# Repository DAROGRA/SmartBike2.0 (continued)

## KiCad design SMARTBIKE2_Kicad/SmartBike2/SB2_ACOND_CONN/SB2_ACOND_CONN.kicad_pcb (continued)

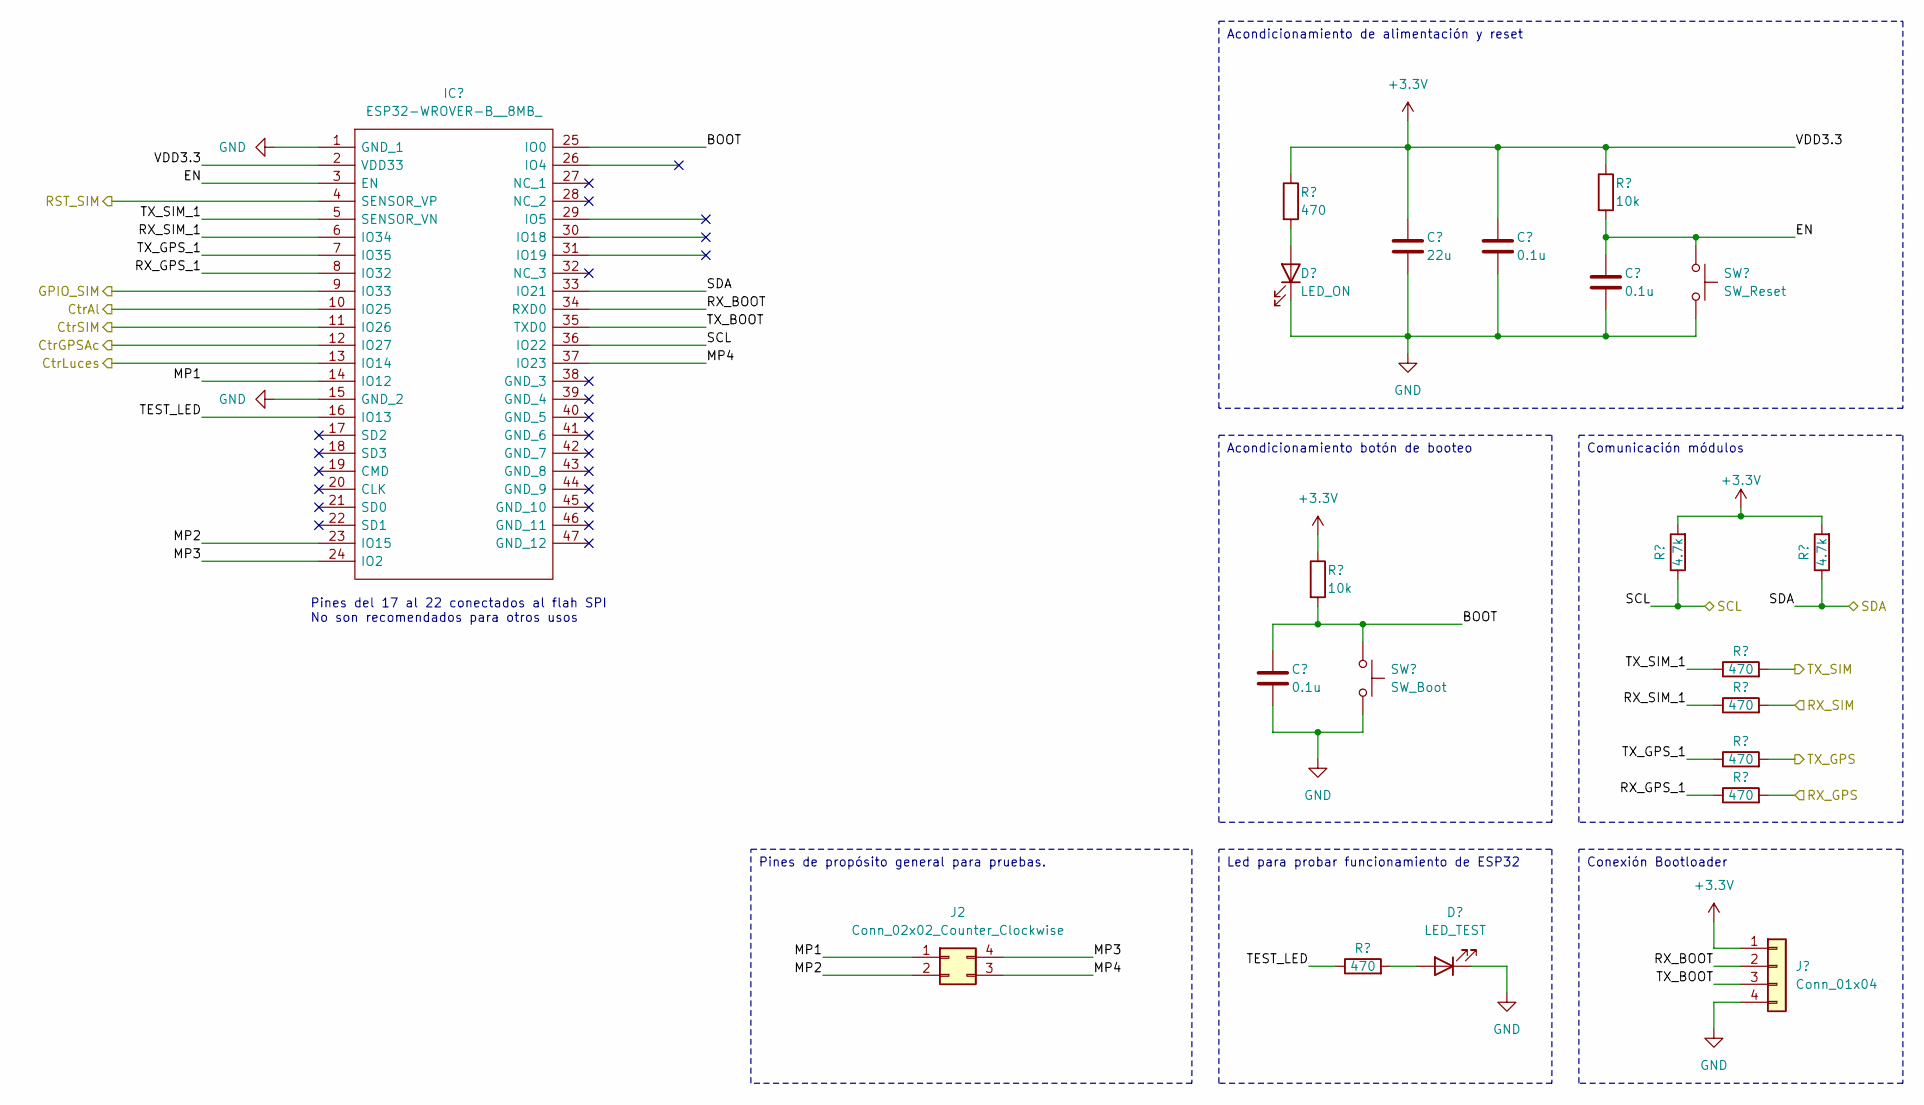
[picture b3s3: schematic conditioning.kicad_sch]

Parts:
C1, C3, C4: 0.1u; C_0805_2012Metric_Pad1.18x1.45mm_HandSolder
C2: 22u; C_0805_2012Metric_Pad1.18x1.45mm_HandSolder
D1: LED_ON; LED_1206_3216Metric_Pad1.42x1.75mm_HandSolder
D2: LED_TEST; LED_1206_3216Metric_Pad1.42x1.75mm_HandSolder
IC1: ESP32-WROVER-B__8MB_; ESP32WROVERB8MB; Manufacturer_Part_Number ESP32-WROVER-B (8MB); Mouser Part Number 356-ESP32-WRO-B(8MB)
J2: Conn_02x02_Counter_Clockwise; PinHeader_2x02_P2.54mm_Vertical
J3: Conn_01x04; PinSocket_1x04_P2.54mm_Vertical
R1, R3, R6, R7, R8, R9: 470; R_0805_2012Metric_Pad1.20x1.40mm_HandSolder
R2, R4: 10k; R_0805_2012Metric_Pad1.20x1.40mm_HandSolder
R5, R10: 4.7k; R_0805_2012Metric_Pad1.20x1.40mm_HandSolder
SW1: SW_Boot; SW_SPST_CK_RS282G05A3
SW2: SW_Reset; SW_SPST_CK_RS282G05A3

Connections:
+3.3V: C2.1, C3.1, IC1.2 (VDD33), J3.1, R1.1, R2.1, R4.1, R5.2, R10.2; also elsewhere on the board
/Acondicionamiento/BOOT: C1.1, IC1.25 (IO0), R2.2, SW1.2
/Acondicionamiento/CtrAl: IC1.10 (IO25); also elsewhere on the board
/Acondicionamiento/CtrGPSAc: IC1.12 (IO27); also elsewhere on the board
/Acondicionamiento/CtrLuces: IC1.13 (IO14); also elsewhere on the board
/Acondicionamiento/CtrSIM: IC1.11 (IO26); also elsewhere on the board
/Acondicionamiento/EN: C4.1, IC1.3 (EN), R4.2, SW2.1
/Acondicionamiento/GPIO_SIM: IC1.9 (IO33); also elsewhere on the board
/Acondicionamiento/MP1: IC1.14 (IO12), J2.1
/Acondicionamiento/MP2: IC1.23 (IO15), J2.2
/Acondicionamiento/MP3: IC1.24 (IO2), J2.4
/Acondicionamiento/MP4: IC1.37 (IO23), J2.3
/Acondicionamiento/RST_SIM: IC1.4 (SENSOR_VP); also elsewhere on the board
/Acondicionamiento/RX_BOOT: IC1.34 (RXD0), J3.2
/Acondicionamiento/RX_GPS: R9.2; also elsewhere on the board
/Acondicionamiento/RX_GPS_1: IC1.8 (IO32), R9.1
/Acondicionamiento/RX_SIM: R7.2; also elsewhere on the board
/Acondicionamiento/RX_SIM_1: IC1.6 (IO34), R7.1
/Acondicionamiento/SCL: IC1.36 (IO22), R5.1; also elsewhere on the board
/Acondicionamiento/SDA: IC1.33 (IO21), R10.1; also elsewhere on the board
/Acondicionamiento/TEST_LED: IC1.16 (IO13), R3.1
/Acondicionamiento/TX_BOOT: IC1.35 (TXD0), J3.3
/Acondicionamiento/TX_GPS: R8.2; also elsewhere on the board
/Acondicionamiento/TX_GPS_1: IC1.7 (IO35), R8.1
/Acondicionamiento/TX_SIM: R6.2; also elsewhere on the board
/Acondicionamiento/TX_SIM_1: IC1.5 (SENSOR_VN), R6.1
GND: C1.2, C2.2, C3.2, C4.2, D1.1 (K), D2.1 (K), IC1.1 (GND_1), IC1.15 (GND_2), J3.4, SW1.1, SW2.2; also elsewhere on the board
unnamed: D1.2 (A), R1.2
unnamed: D2.2 (A), R3.2

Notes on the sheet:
Acondicionamiento de alimentación y reset
Led para probar funcionamiento de ESP32
Comunicación módulos
Conexión Bootloader
Acondicionamiento botón de booteo
Pines de propósito general para pruebas.
Pines del 17 al 22 conectados al flah SPI No son recomendados para otros usos

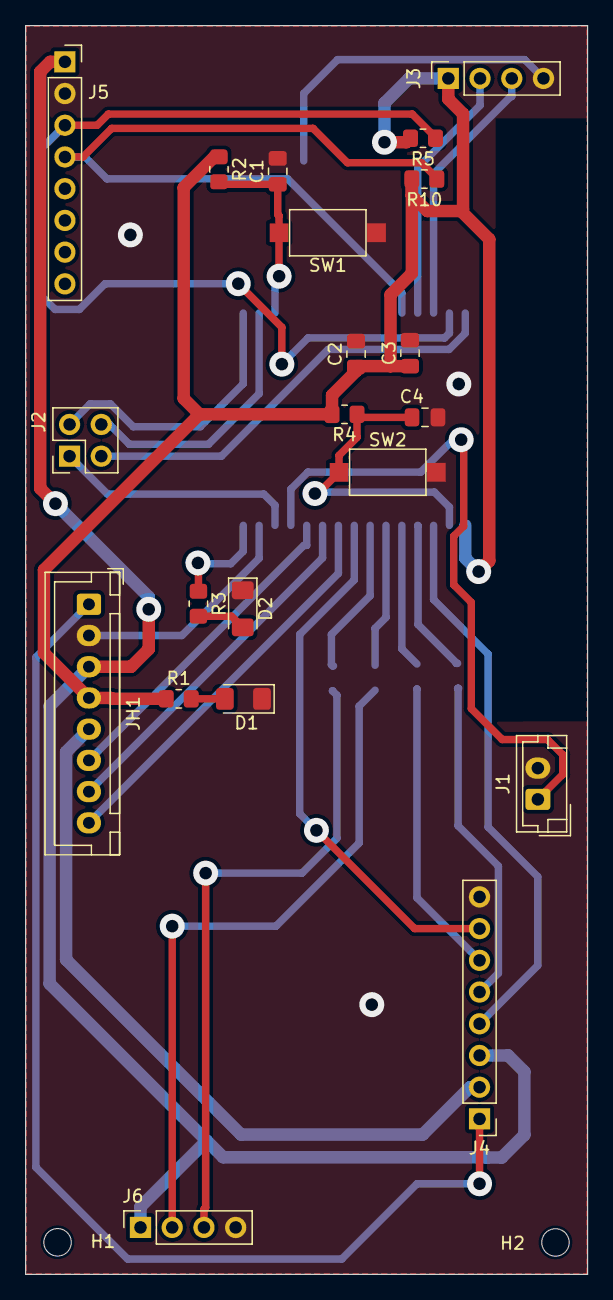
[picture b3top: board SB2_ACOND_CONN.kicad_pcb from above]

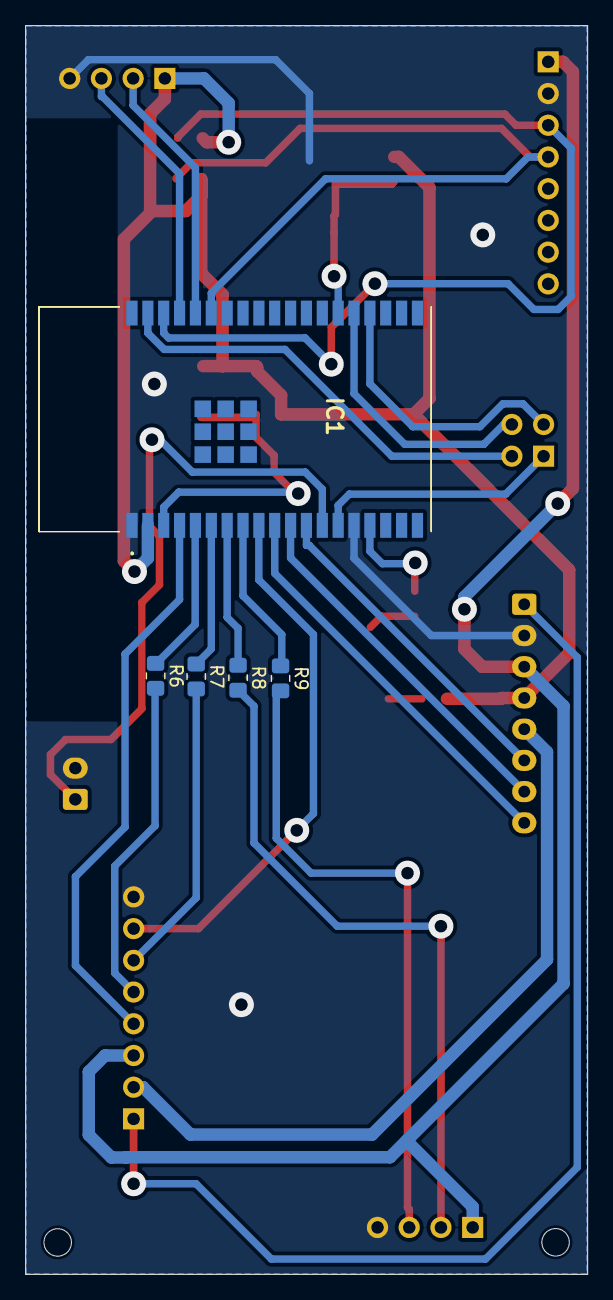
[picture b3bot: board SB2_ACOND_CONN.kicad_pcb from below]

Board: 2 copper layers, 45.0 x 100.0 mm, 28 parts (5 on the bottom side), 32 nets.

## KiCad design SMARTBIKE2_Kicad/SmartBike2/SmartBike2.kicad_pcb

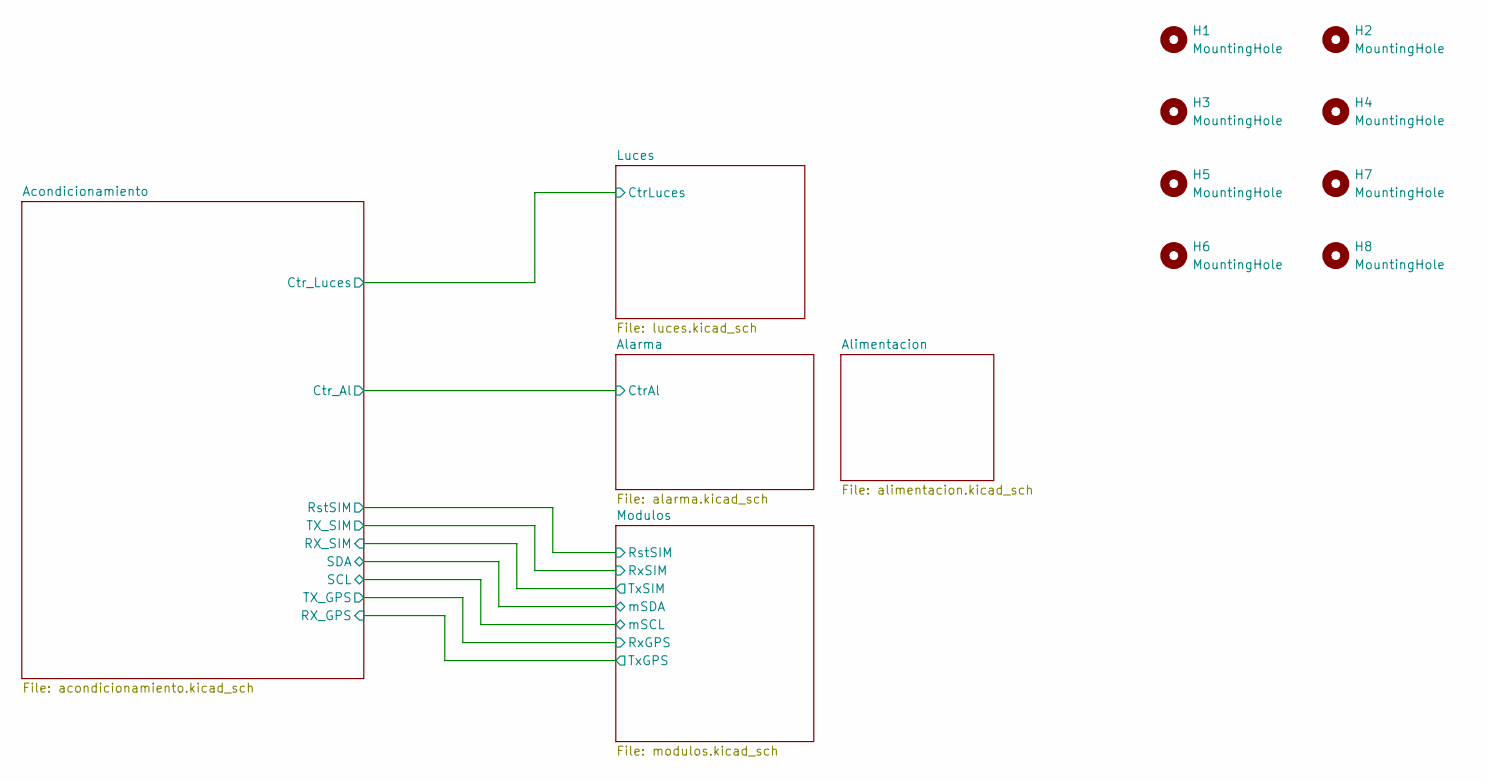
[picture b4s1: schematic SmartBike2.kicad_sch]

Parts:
H1, H2, H3, H4, H5, H6, H7, H8: MountingHole; MountingHole_3.2mm_M3

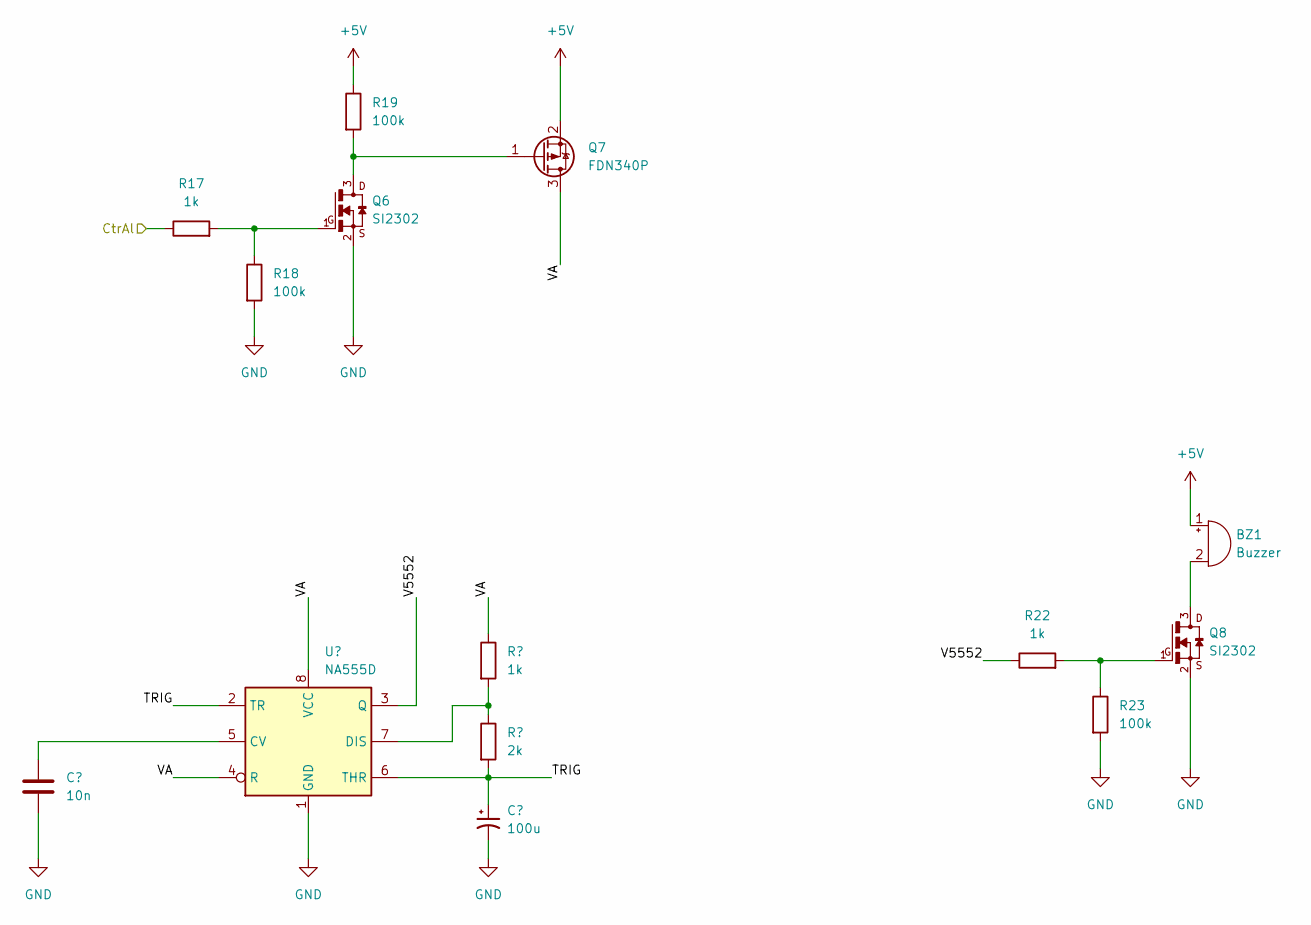
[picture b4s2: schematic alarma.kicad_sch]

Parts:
BZ1: Buzzer; PinHeader_1x02_P2.54mm_Vertical
C12: 10n; C_0805_2012Metric_Pad1.18x1.45mm_HandSolder
C13: 100u; CP_Elec_6.3x5.4
Q6, Q8: SI2302; SOT-23
Q7: FDN340P; SuperSOT-3
R17, R20, R22: 1k; R_0805_2012Metric_Pad1.20x1.40mm_HandSolder
R18, R19, R23: 100k; R_0805_2012Metric_Pad1.20x1.40mm_HandSolder
R21: 2k; R_0805_2012Metric_Pad1.20x1.40mm_HandSolder
U5: NA555D; SOIC-8_3.9x4.9mm_P1.27mm

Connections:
+5V: BZ1.1 (-), Q7.2 (S), R19.1; also elsewhere on the board
/Acondicionamiento/Ctr_Al: R17.1; also elsewhere on the board
/Alarma/TRIG: C13.1, R21.2, U5.2 (TR), U5.6 (THR)
/Alarma/V5552: R22.1, U5.3 (Q)
/Alarma/VA: Q7.3 (D), R20.1, U5.4 (R), U5.8 (VCC)
GND: C12.2, C13.2, Q6.2, Q8.2, R18.2, R23.2, U5.1 (GND); also elsewhere on the board
unnamed: BZ1.2 (+), Q8.3
unnamed: Q6.1, R17.2, R18.1
unnamed: Q6.3, Q7.1 (G), R19.2
unnamed: Q8.1, R22.2, R23.1
unnamed: C12.1, U5.5 (CV)
unnamed: R20.2, R21.1, U5.7 (DIS)

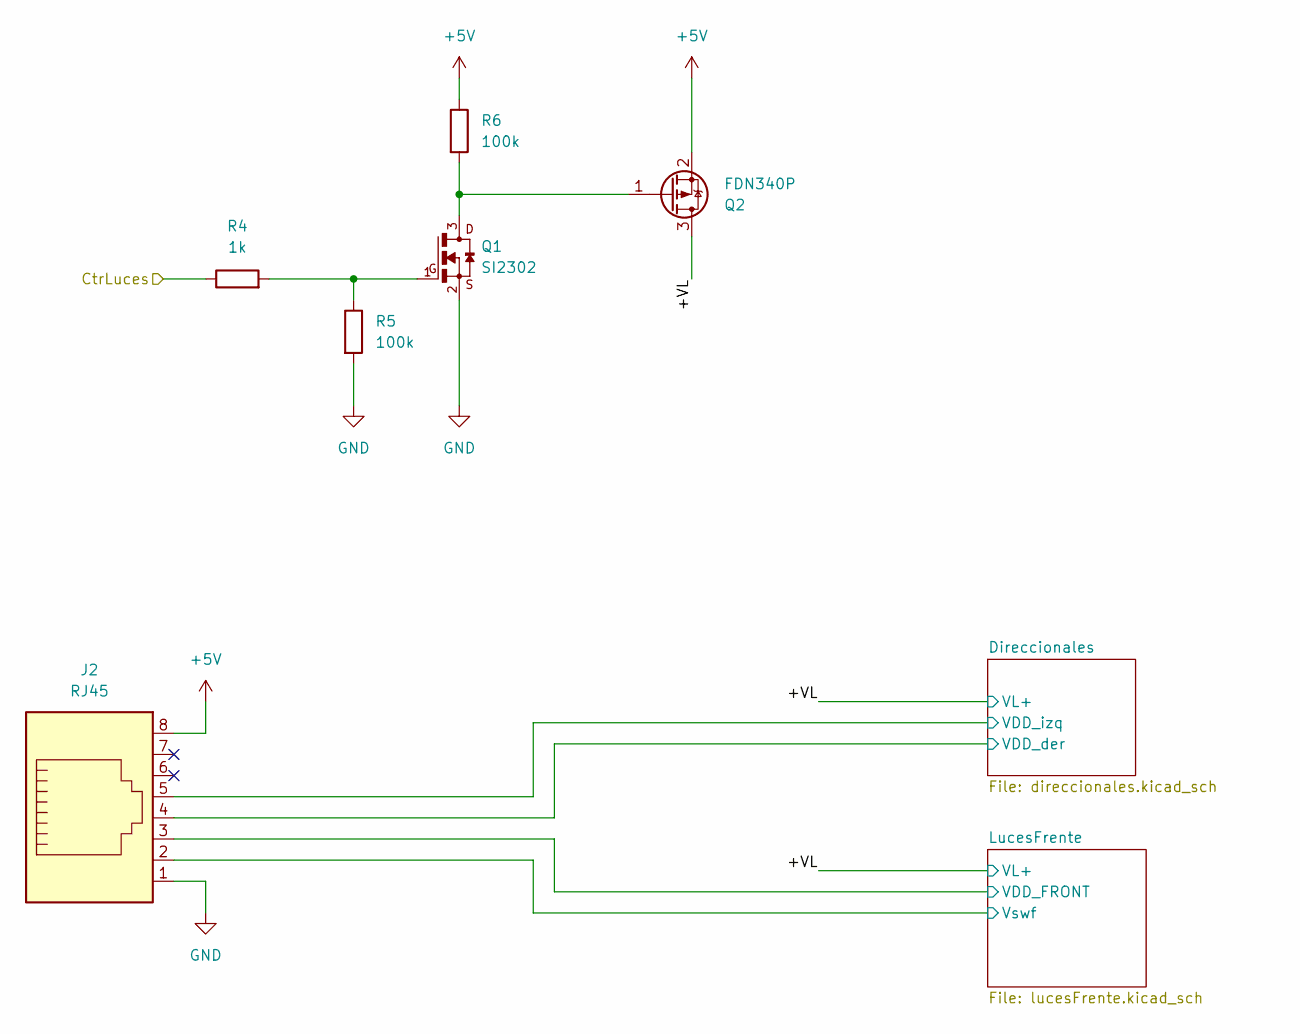
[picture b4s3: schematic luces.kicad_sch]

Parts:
J2: RJ45; RJ45_Amphenol_RJHSE538X
Q1: SI2302; SOT-23
Q2: FDN340P; SuperSOT-3
R4: 1k; R_0805_2012Metric_Pad1.20x1.40mm_HandSolder
R5, R6: 100k; R_0805_2012Metric_Pad1.20x1.40mm_HandSolder

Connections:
+5V: J2.8, Q2.2 (S), R6.1; also elsewhere on the board
/Acondicionamiento/Ctr_Luces: R4.1; also elsewhere on the board
/Luces/+VL: Q2.3 (D); also elsewhere on the board
/Luces/Direccionales/VDD_der: J2.4; also elsewhere on the board
/Luces/Direccionales/VDD_izq: J2.5; also elsewhere on the board
/Luces/LucesFrente/VDD_FRONT: J2.3; also elsewhere on the board
/Luces/LucesFrente/Vswf: J2.2; also elsewhere on the board
GND: J2.1, Q1.2, R5.2; also elsewhere on the board
unnamed: Q1.1, R4.2, R5.1
unnamed: Q1.3, Q2.1 (G), R6.2

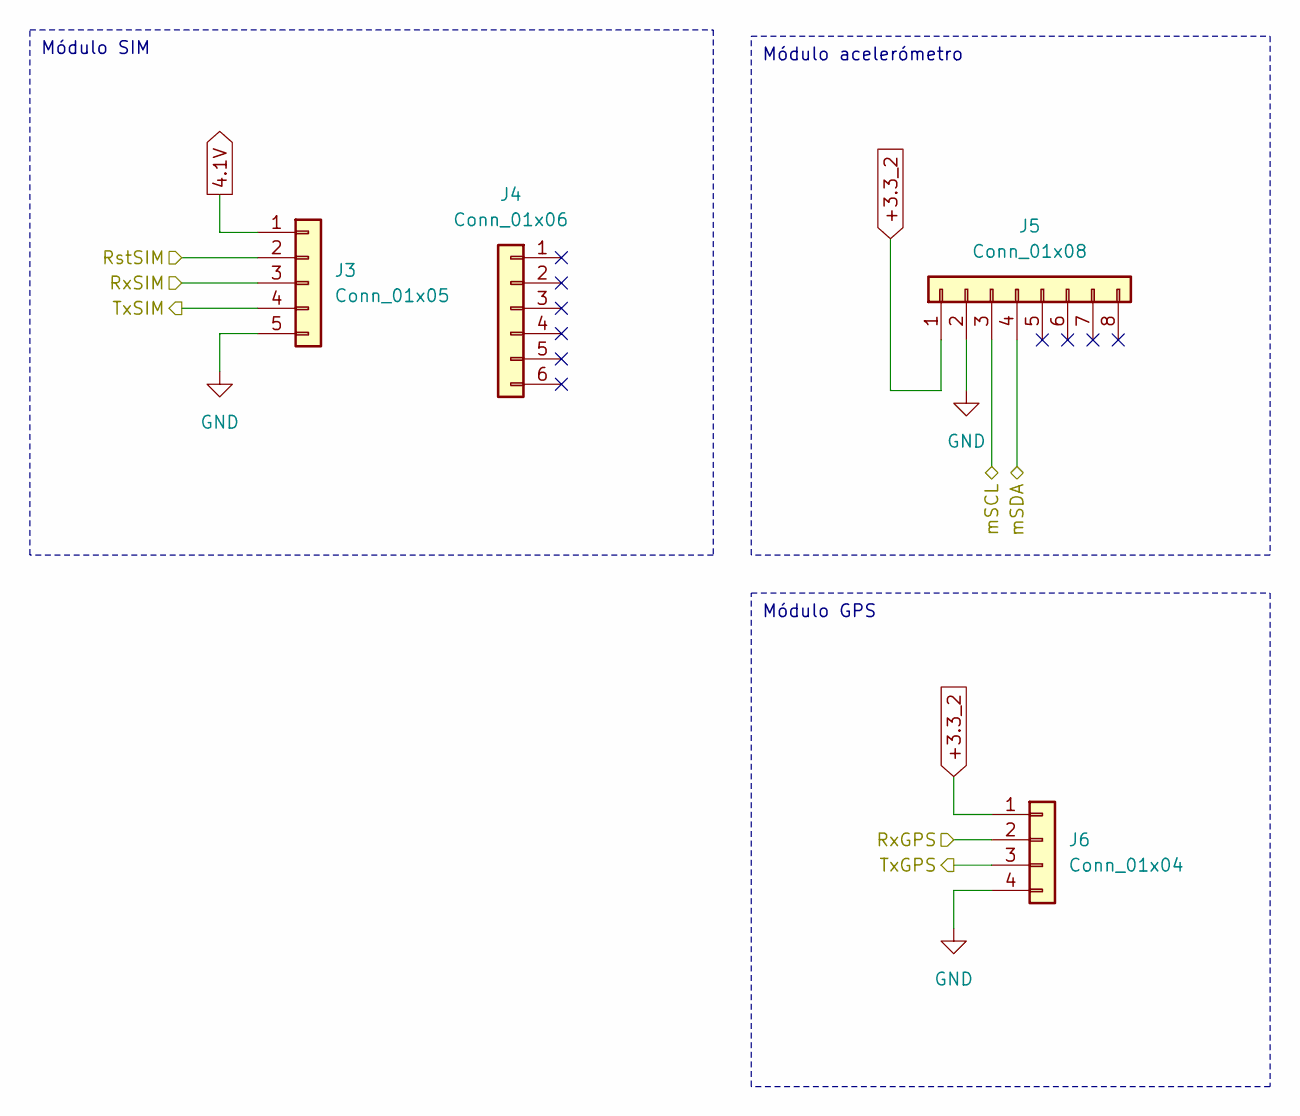
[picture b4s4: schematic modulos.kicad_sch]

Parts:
J3: Conn_01x05; PinSocket_1x05_P2.54mm_Vertical
J4: Conn_01x06; PinSocket_1x06_P2.54mm_Vertical
J5: Conn_01x08; PinSocket_1x08_P2.54mm_Vertical
J6: Conn_01x04; PinSocket_1x04_P2.54mm_Vertical

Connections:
4.1V: J3.1; also elsewhere on the board
+3.3_2: J5.1, J6.1; also elsewhere on the board
/Acondicionamiento/RX_GPS: J6.3; also elsewhere on the board
/Acondicionamiento/RX_SIM: J3.4; also elsewhere on the board
/Acondicionamiento/RstSIM: J3.2; also elsewhere on the board
/Acondicionamiento/SCL: J5.3; also elsewhere on the board
/Acondicionamiento/SDA: J5.4; also elsewhere on the board
/Acondicionamiento/TX_GPS: J6.2; also elsewhere on the board
/Acondicionamiento/TX_SIM: J3.3; also elsewhere on the board
GND: J3.5, J5.2, J6.4; also elsewhere on the board

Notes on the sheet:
Módulo GPS
Módulo SIM
Módulo acelerómetro

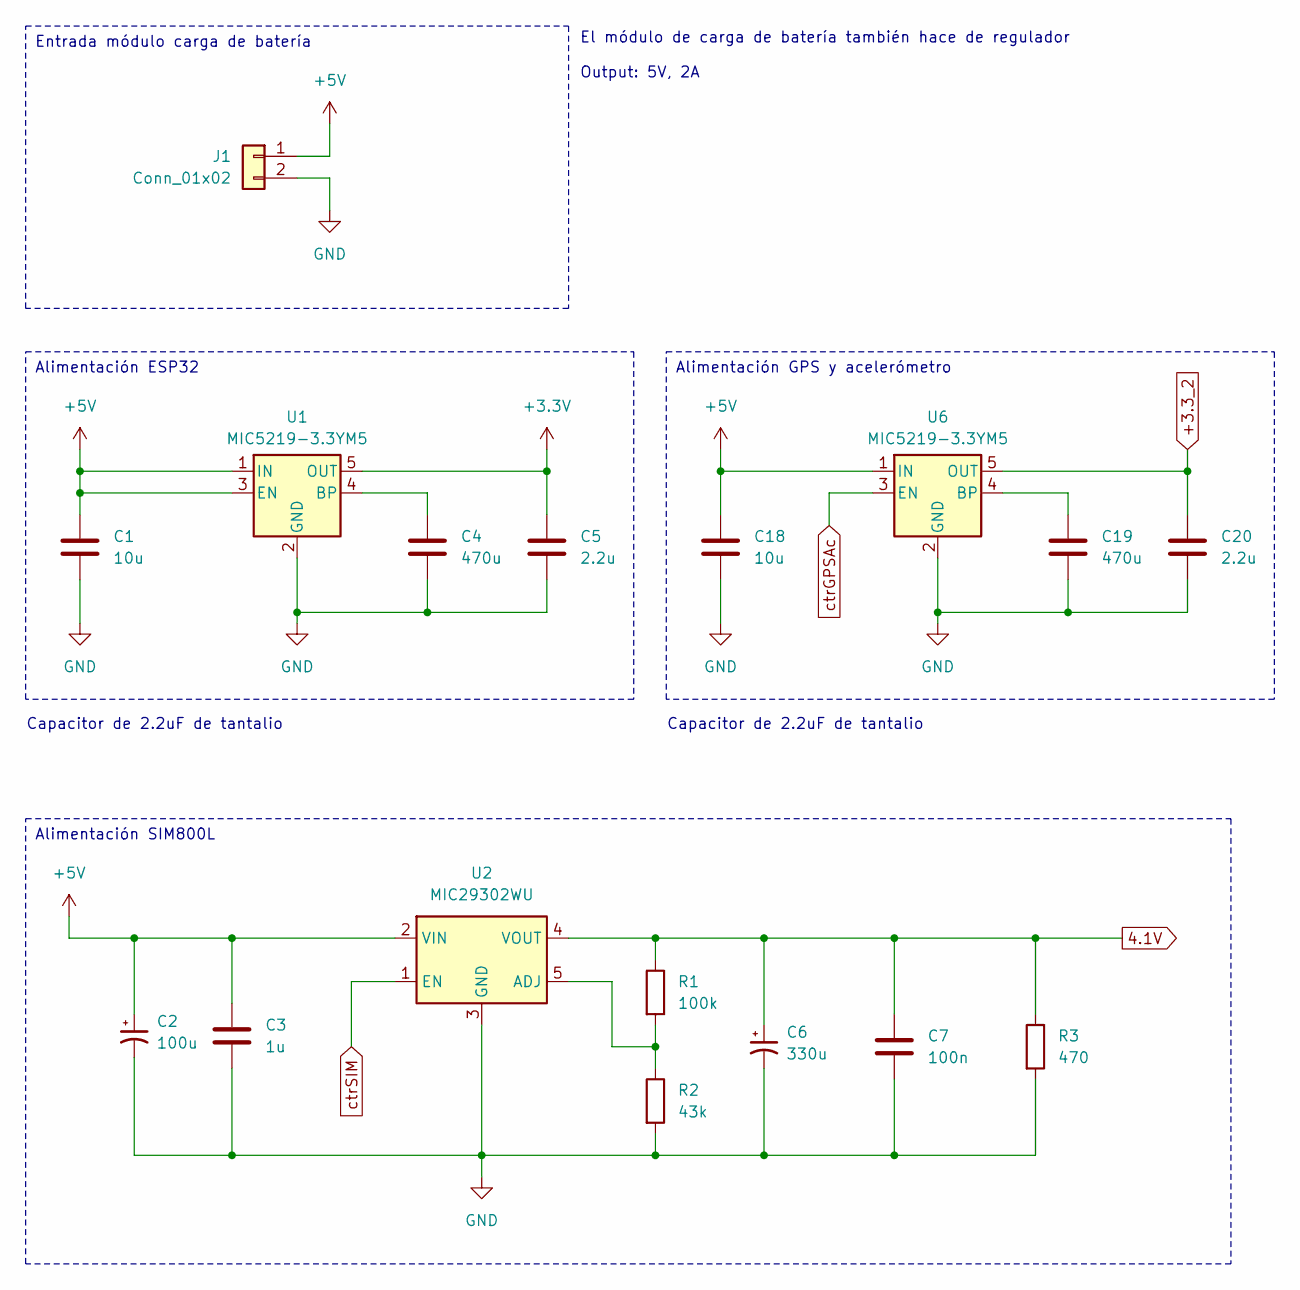
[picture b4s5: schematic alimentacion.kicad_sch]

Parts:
C1, C18: 10u; C_1206_3216Metric_Pad1.33x1.80mm_HandSolder
C2: 100u; CP_Elec_6.3x5.4
C3: 1u; C_0805_2012Metric_Pad1.18x1.45mm_HandSolder
C4, C19: 470u; C_Elec_8x10.2
C5: 2.2u; CP_EIA-3216-10_Kemet-I_Pad1.58x1.35mm_HandSolder
C6: 330u; CP_Elec_8x10
C7: 100n; C_0805_2012Metric_Pad1.18x1.45mm_HandSolder
C20: 2.2u; CP_EIA-3216-18_Kemet-A_Pad1.58x1.35mm_HandSolder
J1: Conn_01x02; JST_EH_B2B-EH-A_1x02_P2.50mm_Vertical
R1: 100k; R_0805_2012Metric_Pad1.20x1.40mm_HandSolder
R2: 43k; R_0805_2012Metric_Pad1.20x1.40mm_HandSolder
R3: 470; R_0805_2012Metric_Pad1.20x1.40mm_HandSolder
U1, U6: MIC5219-3.3YM5; SOT-23-5
U2: MIC29302WU; TO-263-5_TabPin3

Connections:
4.1V: C6.1, C7.1, R1.1, R3.1, U2.4 (VOUT); also elsewhere on the board
+3.3V: C5.1, U1.5 (OUT); also elsewhere on the board
+3.3_2: C20.1, U6.5 (OUT); also elsewhere on the board
+5V: C1.1, C2.1, C3.1, C18.1, J1.1, U1.1 (IN), U1.3 (EN), U2.2 (VIN), U6.1 (IN); also elsewhere on the board
GND: C1.2, C2.2, C3.2, C4.2, C5.2, C6.2, C7.2, C18.2, C19.2, C20.2, J1.2, R2.2, R3.2, U1.2 (GND), U2.3 (GND), U6.2 (GND); also elsewhere on the board
unnamed: C4.1, U1.4 (BP)
unnamed: R1.2, R2.1, U2.5 (ADJ)
unnamed: C19.1, U6.4 (BP)
ctrGPSAc: U6.3 (EN); also elsewhere on the board
ctrSIM: U2.1 (EN); also elsewhere on the board

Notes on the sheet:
Alimentación GPS y acelerómetro
Alimentación SIM800L
Entrada módulo carga de batería
Alimentación ESP32
Capacitor de 2.2uF de tantalio
El módulo de carga de batería también hace de regulador Output: 5V, 2A

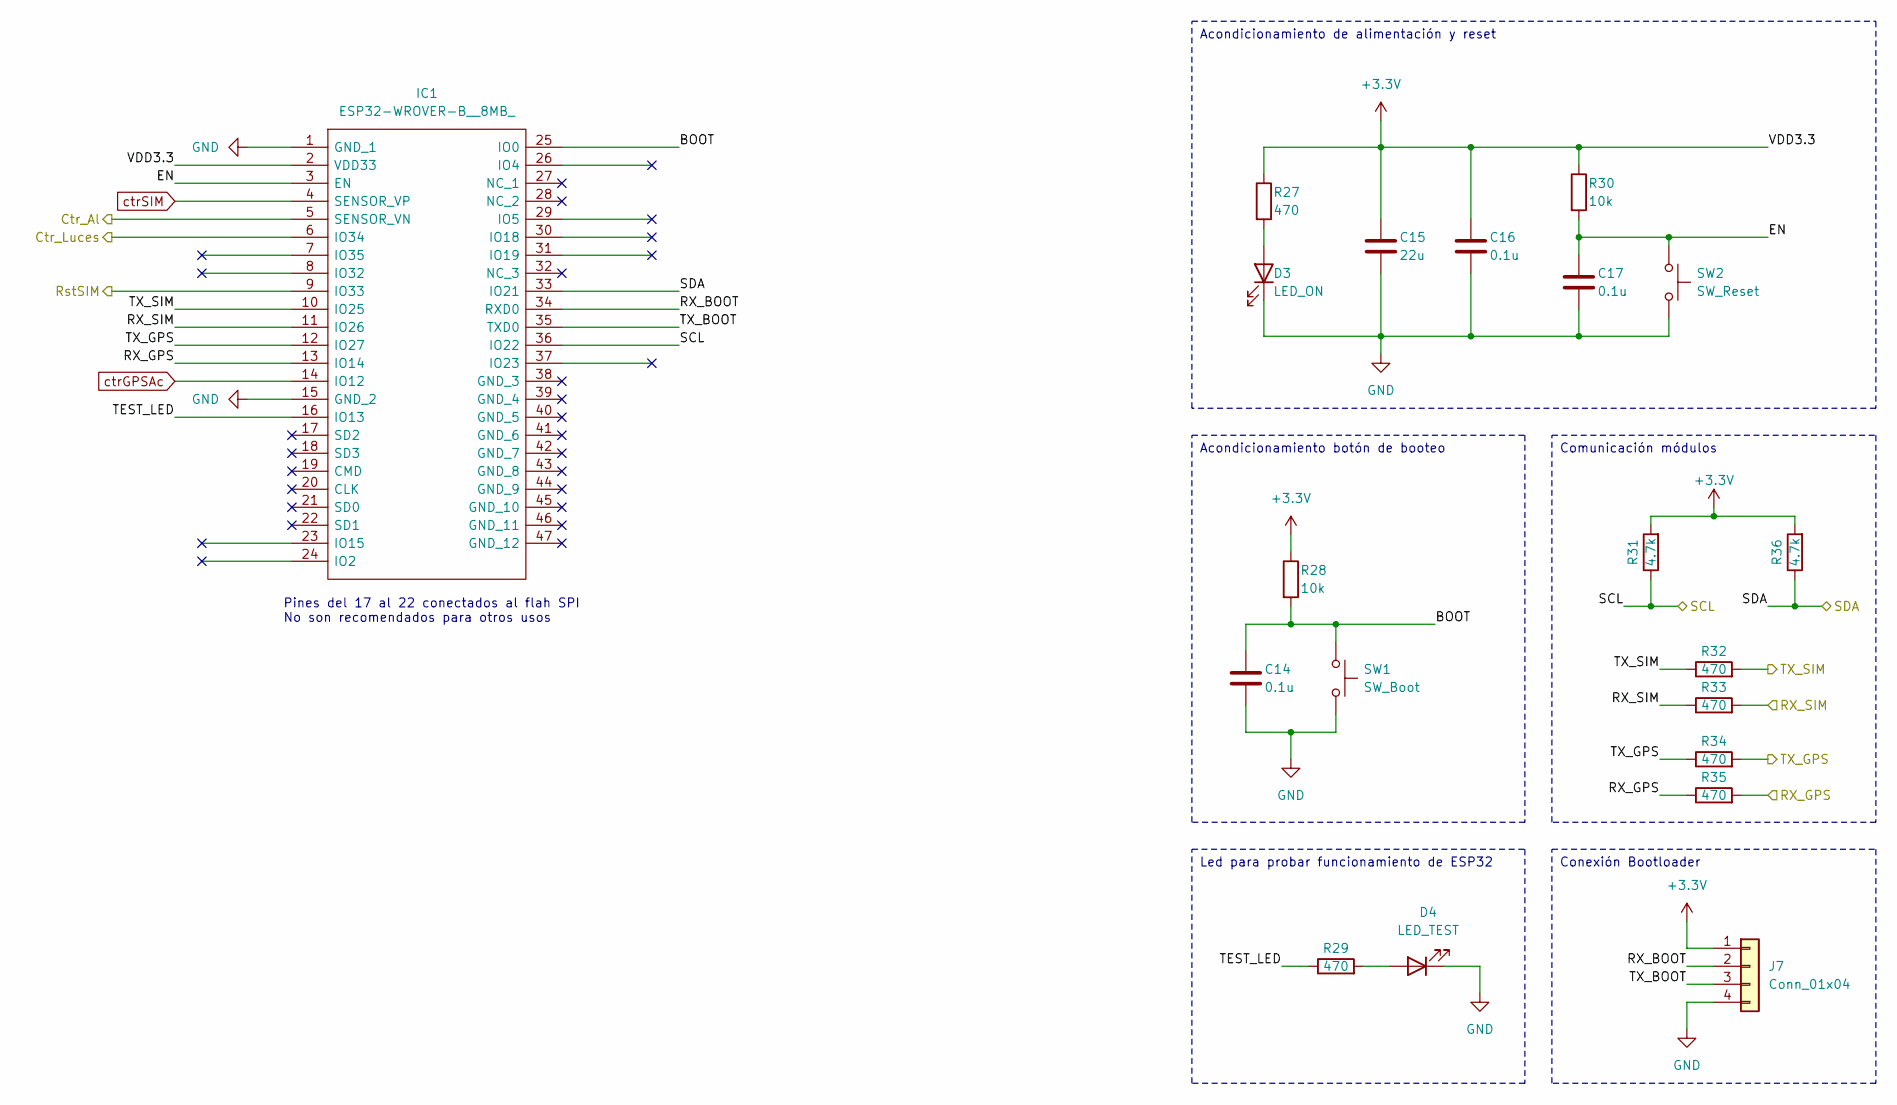
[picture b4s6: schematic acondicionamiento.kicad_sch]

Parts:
C14, C16, C17: 0.1u; C_0805_2012Metric_Pad1.18x1.45mm_HandSolder
C15: 22u; C_0805_2012Metric_Pad1.18x1.45mm_HandSolder
D3: LED_ON; LED_1206_3216Metric_Pad1.42x1.75mm_HandSolder
D4: LED_TEST; LED_1206_3216Metric_Pad1.42x1.75mm_HandSolder
IC1: ESP32-WROVER-B__8MB_; ESP32WROVERB8MB; Manufacturer_Part_Number ESP32-WROVER-B (8MB); Mouser Part Number 356-ESP32-WRO-B(8MB)
J7: Conn_01x04; PinSocket_1x04_P2.54mm_Vertical
R27, R29, R32, R33, R34, R35: 470; R_0805_2012Metric_Pad1.20x1.40mm_HandSolder
R28, R30: 10k; R_0805_2012Metric_Pad1.20x1.40mm_HandSolder
R31, R36: 4.7k; R_0805_2012Metric_Pad1.20x1.40mm_HandSolder
SW1: SW_Boot; SW_SPST_CK_RS282G05A3
SW2: SW_Reset; SW_SPST_CK_RS282G05A3

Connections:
+3.3V: C15.1, C16.1, IC1.2 (VDD33), J7.1, R27.1, R28.1, R30.1, R31.2, R36.2; also elsewhere on the board
/Acondicionamiento/BOOT: C14.1, IC1.25 (IO0), R28.2, SW1.2
/Acondicionamiento/Ctr_Al: IC1.5 (SENSOR_VN); also elsewhere on the board
/Acondicionamiento/Ctr_Luces: IC1.6 (IO34); also elsewhere on the board
/Acondicionamiento/EN: C17.1, IC1.3 (EN), R30.2, SW2.1
/Acondicionamiento/RX_BOOT: IC1.34 (RXD0), J7.2
/Acondicionamiento/RX_GPS: IC1.13 (IO14), R35.1, R35.2; also elsewhere on the board
/Acondicionamiento/RX_SIM: IC1.11 (IO26), R33.1, R33.2; also elsewhere on the board
/Acondicionamiento/RstSIM: IC1.9 (IO33); also elsewhere on the board
/Acondicionamiento/SCL: IC1.36 (IO22), R31.1; also elsewhere on the board
/Acondicionamiento/SDA: IC1.33 (IO21), R36.1; also elsewhere on the board
/Acondicionamiento/TEST_LED: IC1.16 (IO13), R29.1
/Acondicionamiento/TX_BOOT: IC1.35 (TXD0), J7.3
/Acondicionamiento/TX_GPS: IC1.12 (IO27), R34.1, R34.2; also elsewhere on the board
/Acondicionamiento/TX_SIM: IC1.10 (IO25), R32.1, R32.2; also elsewhere on the board
GND: C14.2, C15.2, C16.2, C17.2, D3.1 (K), D4.1 (K), IC1.1 (GND_1), IC1.15 (GND_2), J7.4, SW1.1, SW2.2; also elsewhere on the board
unnamed: D3.2 (A), R27.2
unnamed: D4.2 (A), R29.2
ctrGPSAc: IC1.14 (IO12); also elsewhere on the board
ctrSIM: IC1.4 (SENSOR_VP); also elsewhere on the board

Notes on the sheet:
Comunicación módulos
Conexión Bootloader
Led para probar funcionamiento de ESP32
Acondicionamiento de alimentación y reset
Acondicionamiento botón de booteo
Pines del 17 al 22 conectados al flah SPI No son recomendados para otros usos

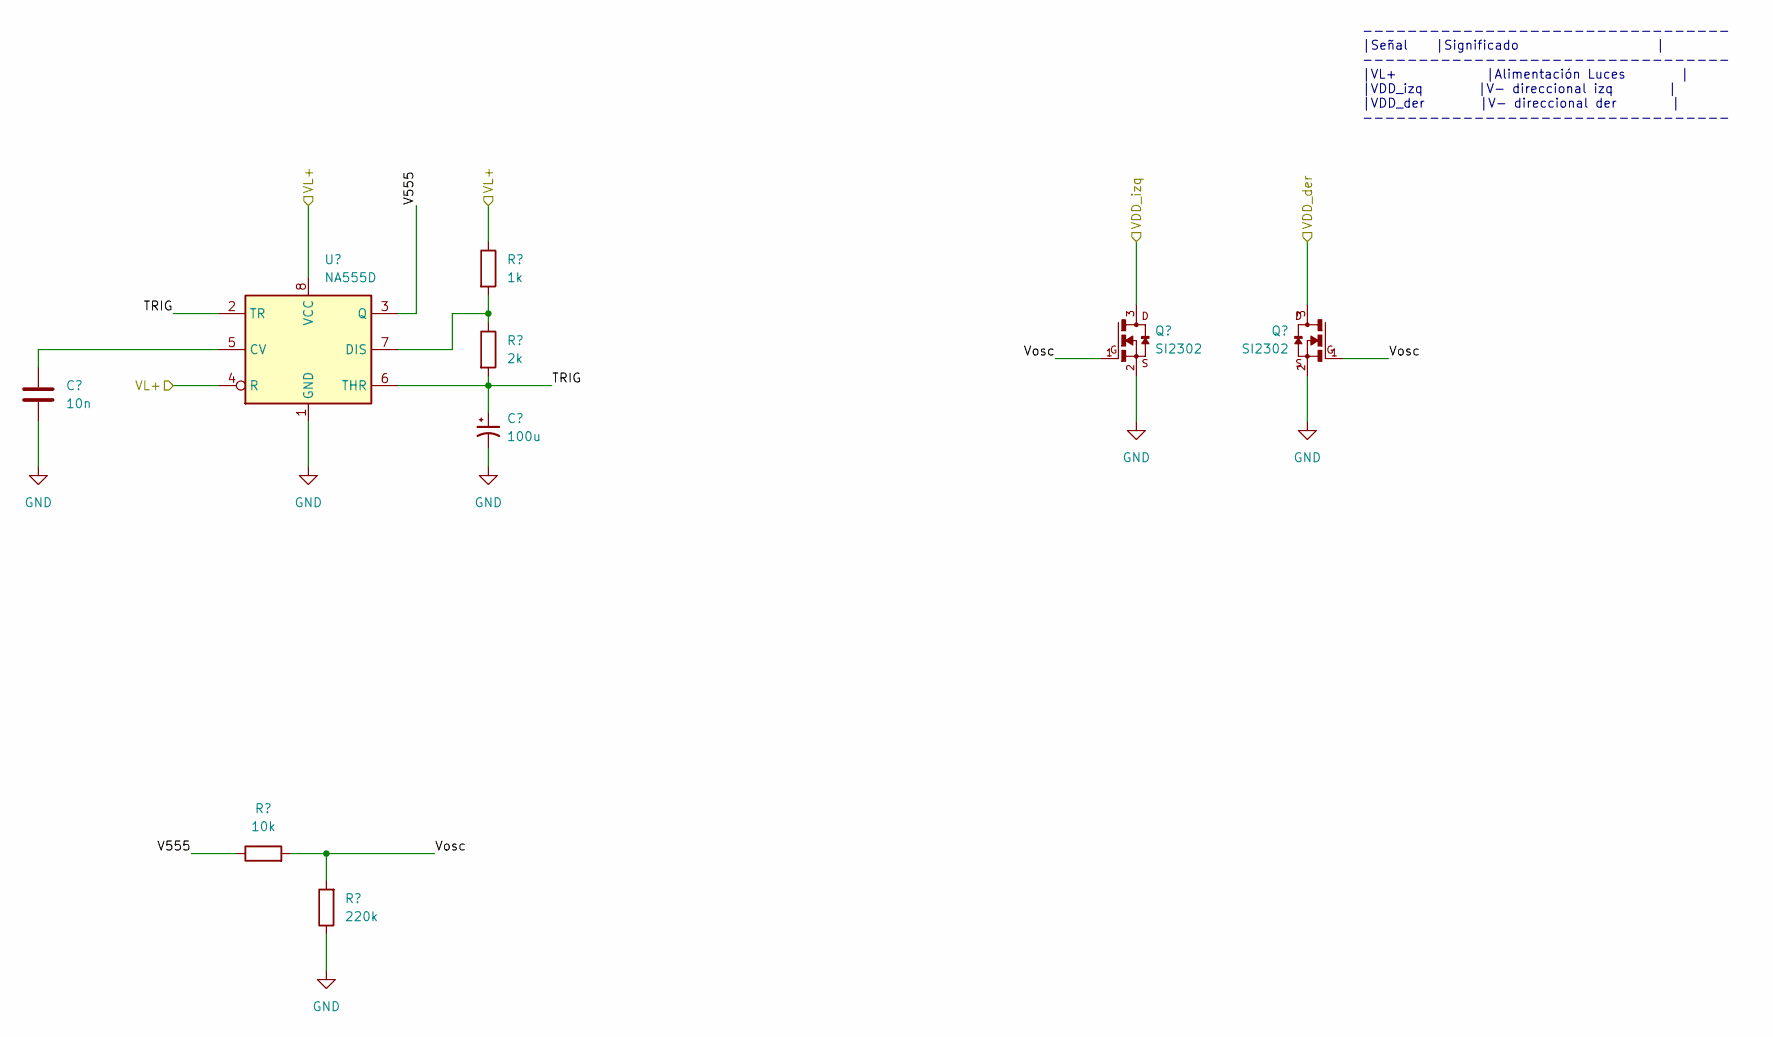
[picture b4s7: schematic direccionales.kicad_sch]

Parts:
C8: 10n; C_0805_2012Metric_Pad1.18x1.45mm_HandSolder
C9: 100u; CP_Elec_6.3x5.4
Q3, Q4: SI2302; SOT-23
R7: 10k; R_0805_2012Metric_Pad1.20x1.40mm_HandSolder
R8: 220k; R_0805_2012Metric_Pad1.20x1.40mm_HandSolder
R9: 1k; R_0805_2012Metric_Pad1.20x1.40mm_HandSolder
R10: 2k; R_0805_2012Metric_Pad1.20x1.40mm_HandSolder
U3: NA555D; SOIC-8_3.9x4.9mm_P1.27mm

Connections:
/Luces/+VL: R9.1, U3.4 (R), U3.8 (VCC); also elsewhere on the board
/Luces/Direccionales/TRIG: C9.1, R10.2, U3.2 (TR), U3.6 (THR)
/Luces/Direccionales/V555: R7.1, U3.3 (Q)
/Luces/Direccionales/VDD_der: Q4.3; also elsewhere on the board
/Luces/Direccionales/VDD_izq: Q3.3; also elsewhere on the board
/Luces/Direccionales/Vosc: Q3.1, Q4.1, R7.2, R8.2
GND: C8.2, C9.2, Q3.2, Q4.2, R8.1, U3.1 (GND); also elsewhere on the board
unnamed: C8.1, U3.5 (CV)
unnamed: R9.2, R10.1, U3.7 (DIS)

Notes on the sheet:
--------------------------------- |Señal |Significado | --------------------------------- |VL+ |Alimentación Luces | |VDD_izq |V- direccional izq | |VDD_der |V- direccional der | ---------------------------------
